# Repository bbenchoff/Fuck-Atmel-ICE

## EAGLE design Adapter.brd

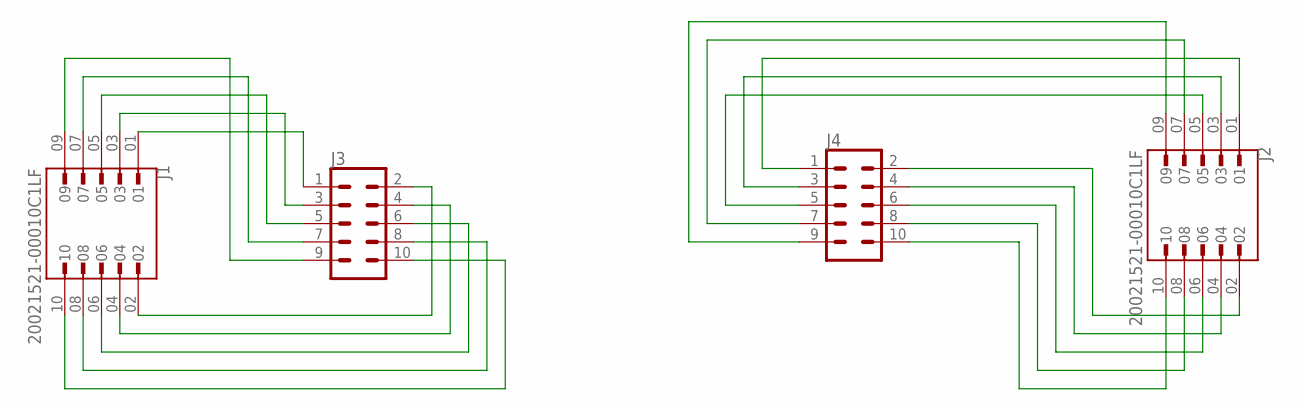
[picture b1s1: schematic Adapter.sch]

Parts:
J1, J2: 20021521-00010C1LF; AMPHENOL_20021521-00010C1LF
J3, J4: CONN_05X2NO_SILK; 2X5_NOSILK

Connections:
unnamed: J1.01, J3.1
unnamed: J1.02, J3.2
unnamed: J1.03, J3.3
unnamed: J1.04, J3.4
unnamed: J1.05, J3.5
unnamed: J1.06, J3.6
unnamed: J1.07, J3.7
unnamed: J1.08, J3.8
unnamed: J1.09, J3.9
unnamed: J1.10, J3.10
unnamed: J2.01, J4.1
unnamed: J2.02, J4.2
unnamed: J2.03, J4.3
unnamed: J2.04, J4.4
unnamed: J2.05, J4.5
unnamed: J2.06, J4.6
unnamed: J2.07, J4.7
unnamed: J2.08, J4.8
unnamed: J2.09, J4.9
unnamed: J2.10, J4.10

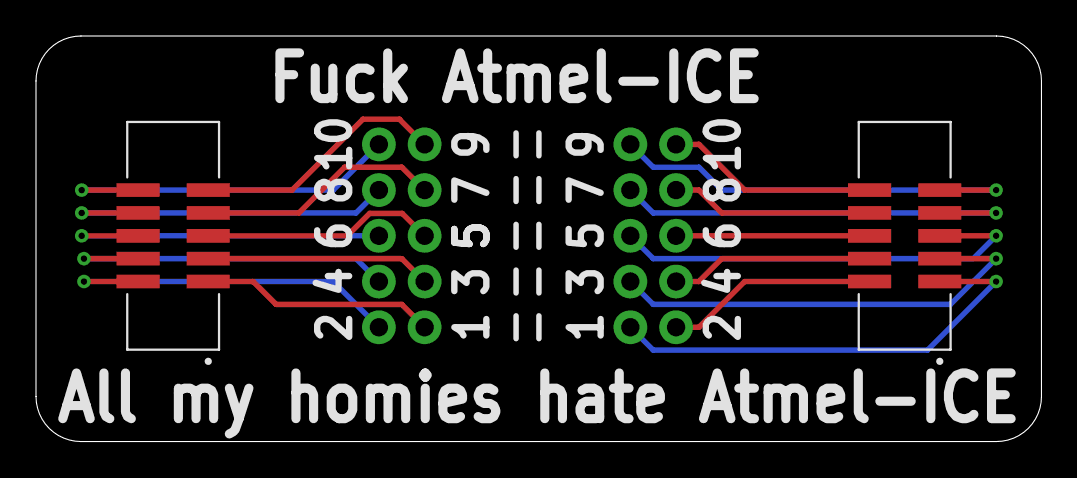
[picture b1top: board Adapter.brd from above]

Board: 2 copper layers, 55.9 x 22.5 mm, 4 parts (1 on the bottom side), 20 nets.

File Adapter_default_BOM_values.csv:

"Qty","Value","Device","Parts","Package","Description","AVAILABILITY","CHECK_PRICES","DESCRIPTION","MF","MP","PACKAGE","PRICE","PURCHASE-URL","SNAPEDA_LINK",
"2","20021521-00010C1LF","20021521-00010C1LF","J1, J2","AMPHENOL_20021521-00010C1LF","Check availability","In Stock","https://www.snapeda.com/parts/20021521-00010C1LF/Amphenol/vi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"," Minitek127®, Shrouded Board to Board Header, Surface Mount, 10 positions, 1.27mm (0.500in) pitch. ","AMPHENOL ICC / FCI","20021521-00010C1LF","None","None","https://www.snapeda.com/api/url_track_click_mouser/?unipart_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 ICC / FCI&part_name=20021521-00010C1LF&search_term=20021521-00010c1lf","https://www.snapeda.com/parts/20021521-00010C1LF/Amphenol/vi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",
"2","","CONN_05X2NO_SILK","J3, J4","2X5_NOSILK","Multi connection point. Often used as Generic Header-pin footprint for 0.1 inch spaced/style header connections","","","","","","","","","",

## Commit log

2024-01-08 initial commit, sent to pcbway
2024-01-09 changed adapter board

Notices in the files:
parts and their libraries:
SparkFun-Connectors: Licensing: Creative Commons ShareAlike 4.0 International - https://creativecommons.org/licenses/by-sa/4.0
